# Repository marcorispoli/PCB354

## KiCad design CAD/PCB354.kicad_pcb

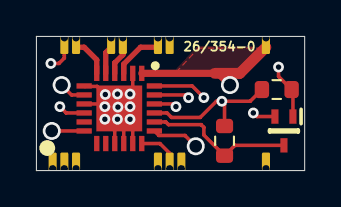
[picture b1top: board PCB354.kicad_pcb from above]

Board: 4 copper layers, 14.9 x 7.5 mm, 19 parts (1 on the bottom side), 16 nets.

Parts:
CPAD1, CPAD2, CPAD3, CPAD10, CPAD11, CPAD12, CPAD14, CPAD15, CPAD18, CPAD19, CPAD22, CPAD23, CPAD26, CPAD27: Castellated_0.45x1
HS1: Heatsink_Pad; TestPoint_Pad_3.0x3.0mm
IC1: DRV8434RGER; DRV8434_QFN50P400X400X100-25N-D
Q1: NTA4153NT1G; MOS_NTA4153NT1G_SC75-3
R1, R2: 10K; R_0603_1608Metric

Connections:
+24V: CPAD26.1 (I_1), IC1.1 (VM_1), IC1.8 (VM_2)
/CPH: CPAD1.1 (I_1), IC1.23 (CPH)
/CPL: CPAD2.1 (I_1), IC1.22 (CPL)
/DIR: CPAD14.1 (I_1), IC1.19 (DIR)
/ENA: IC1.20 (ENABLE), Q1.3 (D), R1.2
/O1A: CPAD15.1 (I_1), IC1.3 (AOUT1)
/O1B: CPAD18.1 (I_1), IC1.4 (AOUT2)
/O2A: CPAD22.1 (I_1), IC1.6 (BOUT1)
/O2B: CPAD19.1 (I_1), IC1.5 (BOUT2)
/STEP: CPAD11.1 (I_1), IC1.18 (STEP)
/VCP: CPAD3.1 (I_1), IC1.24 (VCP)
/VREF: CPAD12.1 (I_1), IC1.12 (VREF)
/_ENA: CPAD23.1 (I_1), Q1.1 (G), R2.2
GND: HS1.1, IC1.2 (PGND_1), IC1.7 (PGND_2), IC1.9 (GND), IC1.15 (DECAY1), IC1.16 (DECAY0), IC1.17 (M1), IC1.25 (EP)
GND1: CPAD27.1 (I_1), Q1.2 (S)
VDD: CPAD10.1 (I_1), IC1.10 (DVDD), IC1.21 (NSLEEP), R1.1, R2.1
